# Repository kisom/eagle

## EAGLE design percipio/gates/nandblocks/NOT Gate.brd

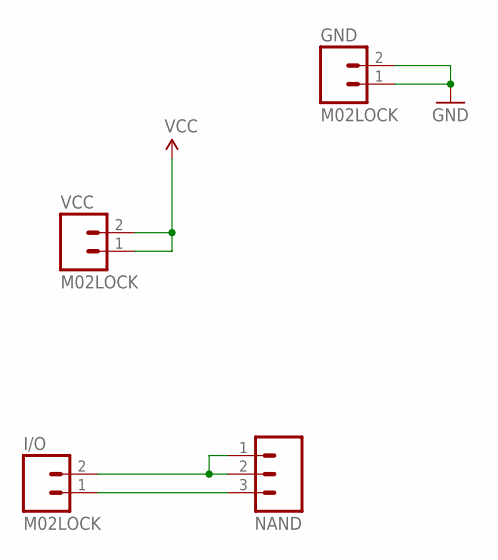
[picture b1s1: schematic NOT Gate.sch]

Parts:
GND: M02LOCK; 1X02_LOCK
I/O: M02LOCK; 1X02_LOCK
NAND: M03LOCK; 1X03_LOCK
VCC: M02LOCK; 1X02_LOCK

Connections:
GND: GND.1, GND.2
unnamed: I/O.2, NAND.1, NAND.2
unnamed: I/O.1, NAND.3
VCC: VCC.1, VCC.2

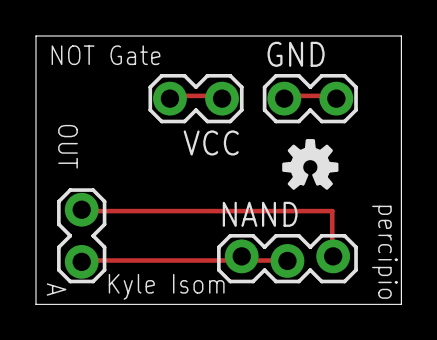
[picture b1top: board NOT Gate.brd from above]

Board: 2 copper layers, 20.3 x 14.9 mm, 5 parts (0 on the bottom side), 4 nets.

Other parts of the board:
U$1: OSHW-LOGO-S

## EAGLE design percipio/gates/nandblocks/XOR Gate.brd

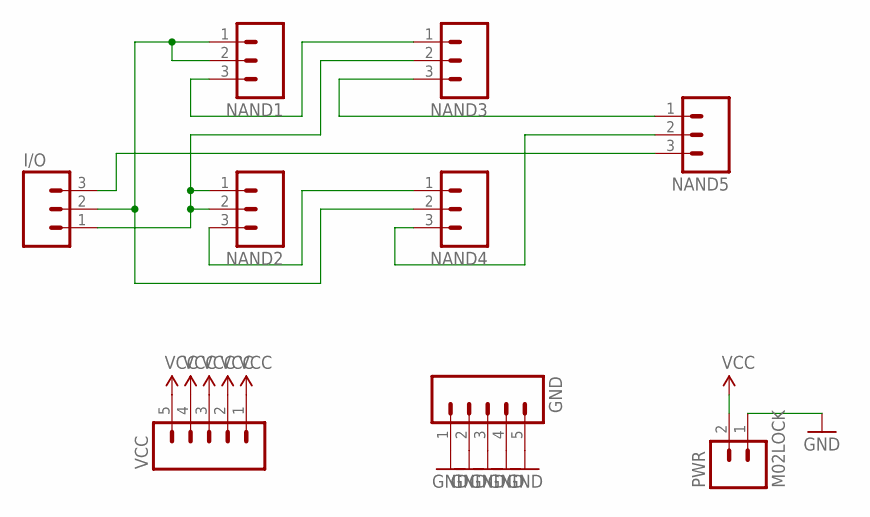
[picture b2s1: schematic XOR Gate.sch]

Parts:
GND: M05LOCK; 1X05_LOCK
I/O: M03LOCK; 1X03_LOCK
NAND1, NAND2, NAND3, NAND4, NAND5: M03LOCK; 1X03_LOCK
PWR: M02LOCK; 1X02_LOCK
VCC: M05LOCK; 1X05_LOCK

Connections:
GND: GND.1, GND.2, GND.3, GND.4, GND.5, PWR.1
unnamed: I/O.3, NAND5.3
unnamed: I/O.2, NAND1.1, NAND1.2, NAND4.2
unnamed: NAND1.3, NAND3.1
unnamed: I/O.1, NAND2.1, NAND2.2, NAND3.2
unnamed: NAND2.3, NAND4.1
unnamed: NAND3.3, NAND5.1
unnamed: NAND4.3, NAND5.2
VCC: PWR.2, VCC.1, VCC.2, VCC.3, VCC.4, VCC.5

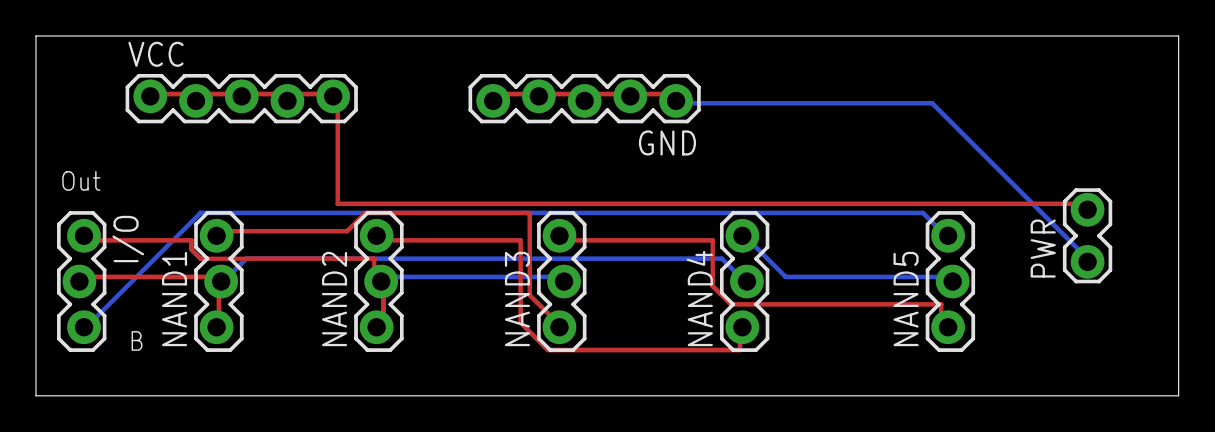
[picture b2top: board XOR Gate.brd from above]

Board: 2 copper layers, 63.5 x 20.0 mm, 9 parts (0 on the bottom side), 9 nets.

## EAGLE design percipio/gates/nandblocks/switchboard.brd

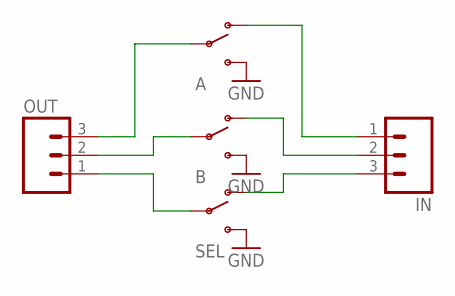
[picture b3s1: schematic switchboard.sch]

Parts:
A: SWITCH-SPDTPTH; SWITCH-SPDT
B: SWITCH-SPDTPTH; SWITCH-SPDT
IN: M03LOCK; 1X03_LOCK
OUT: M03LOCK; 1X03_LOCK
SEL: SWITCH-SPDTPTH; SWITCH-SPDT

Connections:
GND: A.3 (S), B.3 (S), SEL.3 (S)
unnamed: A.2, OUT.3
unnamed: B.2, OUT.2
unnamed: OUT.1, SEL.2
unnamed: A.1 (O), IN.1
unnamed: B.1 (O), IN.2
unnamed: IN.3, SEL.1 (O)

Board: 2 copper layers, 5 parts (0 on the bottom side), 7 nets, no tracks yet.

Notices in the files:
parts and their libraries:
SparkFun-Connectors: Licensing: CC v3.0 Share-Alike You are welcome to use this library for commercial purposes.
